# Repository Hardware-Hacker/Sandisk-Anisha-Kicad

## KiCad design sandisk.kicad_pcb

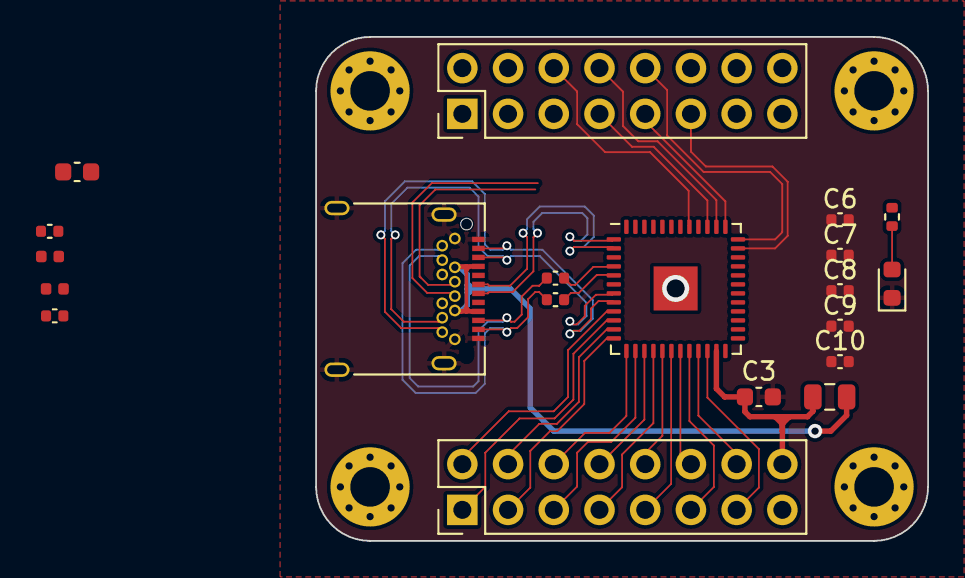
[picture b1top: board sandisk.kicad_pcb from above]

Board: 2 copper layers, 34.0 x 28.0 mm, 24 parts (0 on the bottom side), 37 nets.

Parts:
C1, C2, C4, C5: 100nF; C_0402_1005Metric
C3, C3#2: 6uF; C_0603_1608Metric
C6, C7, C8, C9, C10: C; C_0402_1005Metric
D1: LED; LED_0603_1608Metric
F1: Fuse; Fuse_0805_2012Metric
H1, H2, H3, H4: MountingHole_Pad; MountingHole_2.2mm_M2_Pad_Via
J1: USB_C_Receptacle; USB_C_Receptacle_Amphenol_12401548E4-2A
J2, J3: Conn_02x08_Odd_Even; PinHeader_2x08_P2.54mm_Vertical
L1, L2: L; L_0402_1005Metric
R1: R; R_0402_1005Metric
U1: 20-82-00388

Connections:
+1V8: C6.2, C7.2
+3V3: C8.1, C9.1, J3.15, L2.1, U1.24 (VPHY)
/1V2_HEC: C5.1, L2.2
/3V3_HEC: C4.1, L1.2
/10: J3.4, R1.1
/14: J3.5, U1.14
/15: J3.8, U1.15
/16: J3.7, U1.16
/18: J3.9, U1.18
/19: J3.12, U1.19
/20: J3.11, U1.20
/21: J3.14, U1.21
/22: J3.13, U1.22
/35: J2.11, U1.35
/36: J2.10, U1.36
/37: J2.9, U1.37
/38: J2.8, U1.38
/39: J2.7, U1.39
/41: J2.6, U1.41
/42: J2.5, U1.42
/43: J2.4, U1.43
/45: J2.3, U1.45
/46: J2.2, U1.46
/47: J2.1, U1.47
/SSRXN: C1.1, U1.4 (SSRXM)
/SSRXP: C2.1, U1.5 (SSRXP)
/SSTXN: J1.A3 (TX1-), J1.B3 (TX2-), U1.7 (SSTXM)
/SSTXP: J1.A2 (TX1+), J1.B2 (TX2+), U1.8 (SSTXP)
/TYPEC_RXN: C1.2, J1.A10 (RX2-), J1.B10 (RX1-)
/TYPEC_RXP: C2.2, J1.A11 (RX2+), J1.B11 (RX1+)
/USB_DN: J1.A7 (D-), J1.B7 (D-), U1.1 (USB_DM)
/USB_DP: J1.A6 (D+), J1.B6 (D+), U1.2 (USB_DP)
GND: C3#2.2, C4.2, C5.2, C6.1, C7.1, C8.2, C9.2, C10.1, D1.1 (K), J1.A1 (GND), J1.A12 (GND), J1.B1 (GND), J1.B12 (GND), J1.S1 (SHIELD)
HPAD: U1.26 (GND), U1.49 (HPAD)
unnamed: D1.2 (A), R1.2
unnamed: F1.1, J1.A4 (VBUS), J1.A9 (VBUS), J1.B4 (VBUS), J1.B9 (VBUS)
VBUS: C3#2.1, F1.2, J3.16, U1.23 (VBUS)

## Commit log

2023-01-17 Initial commit.
